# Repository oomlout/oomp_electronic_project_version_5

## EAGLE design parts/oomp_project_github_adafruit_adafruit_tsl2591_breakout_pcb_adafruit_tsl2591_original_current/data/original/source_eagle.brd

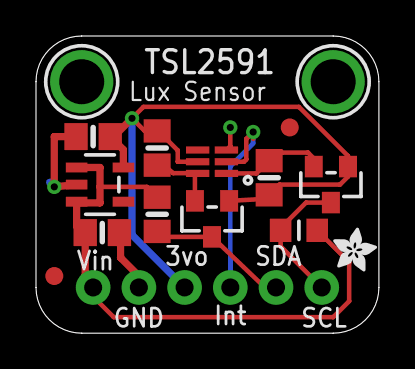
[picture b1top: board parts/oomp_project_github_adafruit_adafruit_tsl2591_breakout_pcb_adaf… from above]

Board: 2 copper layers, 19.1 x 16.5 mm, 17 parts (1 on the bottom side), 8 nets.

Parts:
C2, C3: 10uF; 0805-NO
FID1, FID2: FIDUCIAL""; FIDUCIAL_1MM
JP1: 1X06_ROUND_FULL_76
Q1, Q2: BSS138; SOT23-WIDE
R2, R3, R4: 10K; 0805-NO
R5: 10K; _0805MP
U1: TSL2591; DFN6_TAOS
U2: MIC5225-3.3; SOT23-5
U$15: ADAFRUIT_2.5MM
U$18, U$19: MOUNTINGHOLE2.5; MOUNTINGHOLE_2.5_PLATED
U$20: ADAFRUIT_5MM

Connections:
3.3V: C3.1, JP1.3, Q1.1, Q2.1, R2.2, R3.2, U1.5, U2.5
GND: C2.2, C3.2, JP1.2, U1.3, U2.2
INT: JP1.4, U1.2
SCL: JP1.6, Q2.3, R5.1
SCL_3V: Q2.2, R3.1, U1.1
SDA: JP1.5, Q1.3, R4.1
SDA_3V: Q1.2, R2.1, U1.6
VIN: C2.1, JP1.1, R4.2, R5.2, U2.1, U2.3

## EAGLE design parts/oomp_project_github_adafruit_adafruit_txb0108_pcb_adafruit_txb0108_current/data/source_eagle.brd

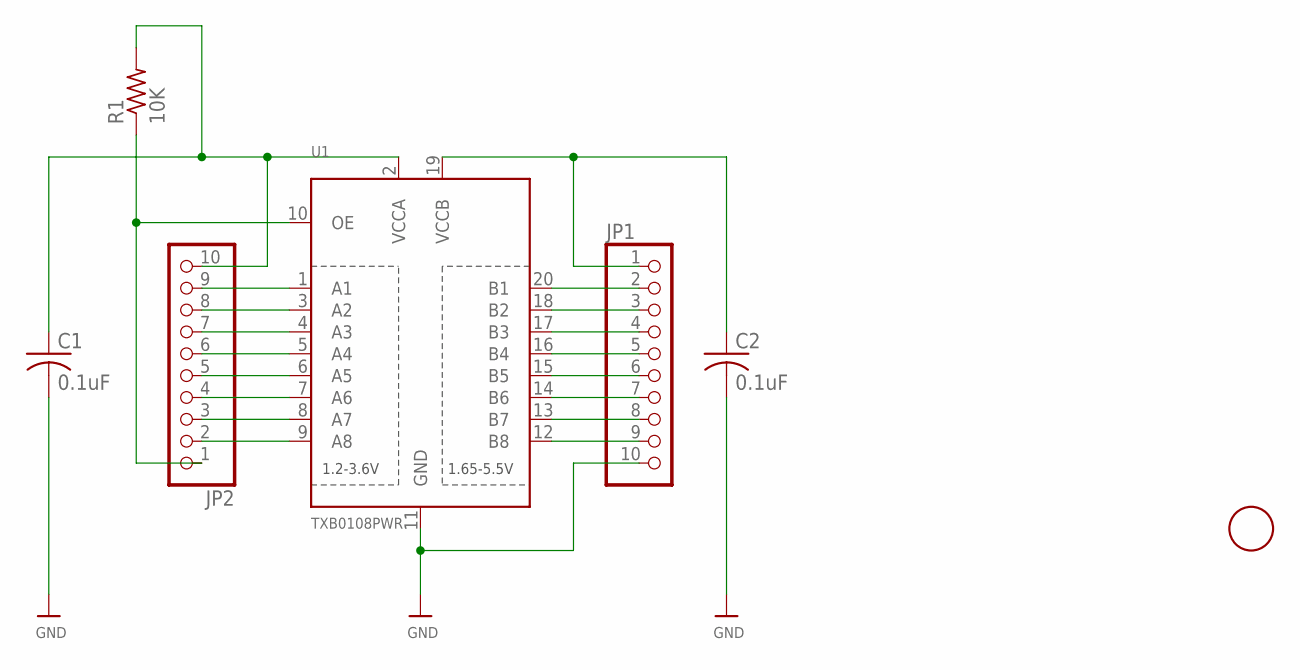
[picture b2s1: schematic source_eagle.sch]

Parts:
C1, C2: 0.1uF; C0805
JP1, JP2: HEADER-1X10THICKER; 1X10_ROUND_76
R1: 10K; R0805
U1: TXB0108PWR; TSSOP20
U$6: FIDUCIAL; FIDUCIAL_1MM

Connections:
GND: C1.2, C2.2, JP1.10, U1.11 (GND)
unnamed: JP1.9, U1.12 (B8)
unnamed: JP1.8, U1.13 (B7)
unnamed: JP1.7, U1.14 (B6)
unnamed: JP1.6, U1.15 (B5)
unnamed: JP1.5, U1.16 (B4)
unnamed: JP1.4, U1.17 (B3)
unnamed: JP1.3, U1.18 (B2)
unnamed: JP1.2, U1.20 (B1)
unnamed: C2.1, JP1.1, U1.19 (VCCB)
unnamed: C1.1, JP2.10, R1.2, U1.2 (VCCA)
unnamed: JP2.9, U1.1 (A1)
unnamed: JP2.8, U1.3 (A2)
unnamed: JP2.7, U1.4 (A3)
unnamed: JP2.6, U1.5 (A4)
unnamed: JP2.5, U1.6 (A5)
unnamed: JP2.4, U1.7 (A6)
unnamed: JP2.3, U1.8 (A7)
unnamed: JP2.2, U1.9 (A8)
unnamed: JP2.1, R1.1, U1.10 (OE)

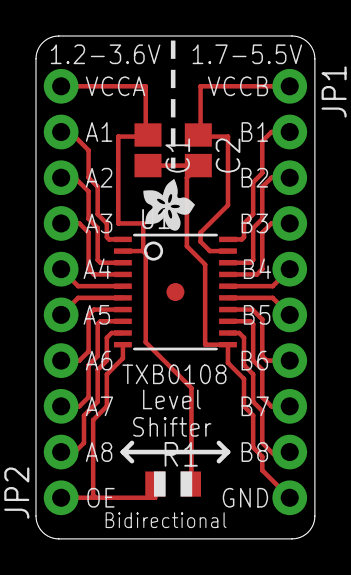
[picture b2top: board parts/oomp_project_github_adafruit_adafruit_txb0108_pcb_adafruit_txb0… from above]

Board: 2 copper layers, 15.5 x 27.9 mm, 8 parts (0 on the bottom side), 20 nets.

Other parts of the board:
U$4: ADAFRUIT200MIL

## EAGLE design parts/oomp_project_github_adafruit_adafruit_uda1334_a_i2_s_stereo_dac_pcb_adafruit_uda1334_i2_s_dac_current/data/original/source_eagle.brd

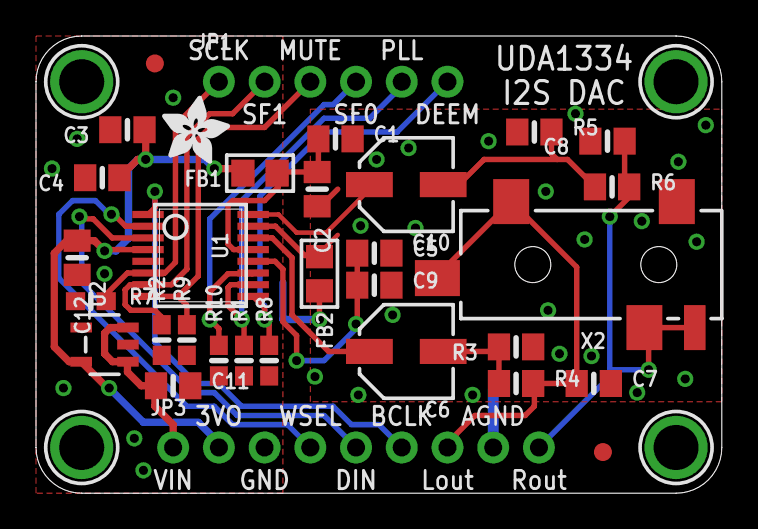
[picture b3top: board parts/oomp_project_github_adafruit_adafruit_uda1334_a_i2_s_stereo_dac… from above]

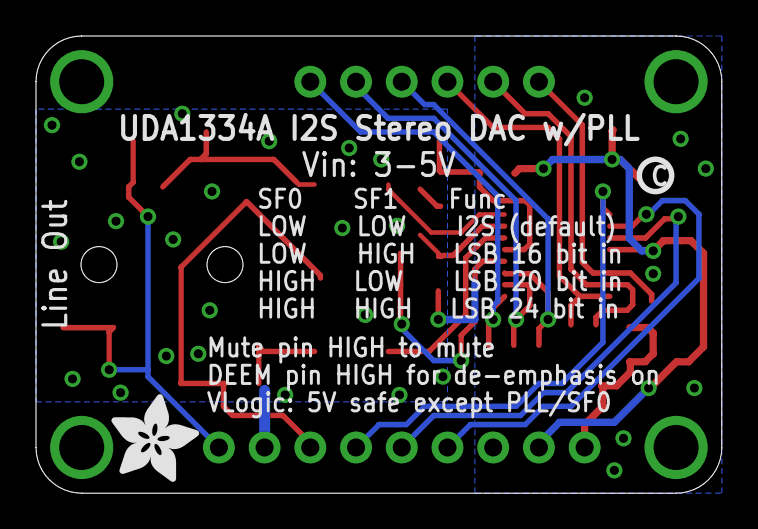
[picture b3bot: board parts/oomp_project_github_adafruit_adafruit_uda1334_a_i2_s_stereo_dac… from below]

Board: 2 copper layers, 38.1 x 25.4 mm, 38 parts (2 on the bottom side), 21 nets.

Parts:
C1, C3, C9: 0.1uF; 0805-NO
C2, C4, C5, C11, C12: 10uF; 0805-NO
C6, C10: 47uF; PANASONIC_C
C7, C8: 0.01uF; 0805-NO
FB1, FB2: Ferrite; 0805
FID1, FID2: FIDUCIAL_1MM
JP1: 1X06_ROUND_70
JP3: 1X09_ROUND_70
R1, R2, R7, R8, R9, R10: 10k; 0603-NO
R3, R5: 220k; 0805-NO
R4, R6: 100; 0805-NO
U1: UDA1334ATS; SSOP16_4.4MM
U2: MIC5225-3.3; SOT23-5
U$5: PCBFEAT-REV-040
U$6: ADAFRUIT_5MM
U$11, U$12, U$13, U$14: MOUNTINGHOLE2.5; MOUNTINGHOLE_2.5_PLATED
U$29: ADAFRUIT_3.5MM
X2: 19269; 4UCONN_19269

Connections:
3.3V: C3.1, C4.1, C12.1, FB1.2, JP3.2, U1.4, U2.5
AGND: C1.2, C2.2, C5.2, C7.2, C8.2, C9.2, FB2.1, JP3.8, R3.1, R5.1, U1.15, X2.1
BITCLK_IN: JP3.6, U1.1
DATA_IN: JP3.5, U1.3
DEEM/CLKOUT: JP1.6, R8.2, U1.9
GND: C3.2, C4.2, C11.2, C12.2, FB2.2, JP3.3, R1.1, R2.1, R7.1, R8.1, R9.1, R10.1, U1.5, U2.2
MUTE: JP1.3, R9.2, U1.8
unnamed: C5.1, C9.1, U1.12
unnamed: C1.1, C2.1, FB1.1, U1.13
unnamed: C10.+, U1.16
unnamed: C6.+, U1.14
unnamed: C6.-, R3.2, R4.1
unnamed: C10.-, R5.2, R6.1
OUTL: C7.1, JP3.7, R4.2, X2.2, X2.4
OUTR: C8.1, JP3.9, R6.2, X2.3, X2.5
PLL_IN: JP1.5, R1.2, U1.10
SFOR0: JP1.4, R10.2, U1.11
SFOR1: JP1.2, R2.2, U1.7
SYSCLK_IN: JP1.1, R7.2, U1.6
VIN: C11.1, JP3.1, U2.1, U2.3
WORDSEL_IN: JP3.4, U1.2

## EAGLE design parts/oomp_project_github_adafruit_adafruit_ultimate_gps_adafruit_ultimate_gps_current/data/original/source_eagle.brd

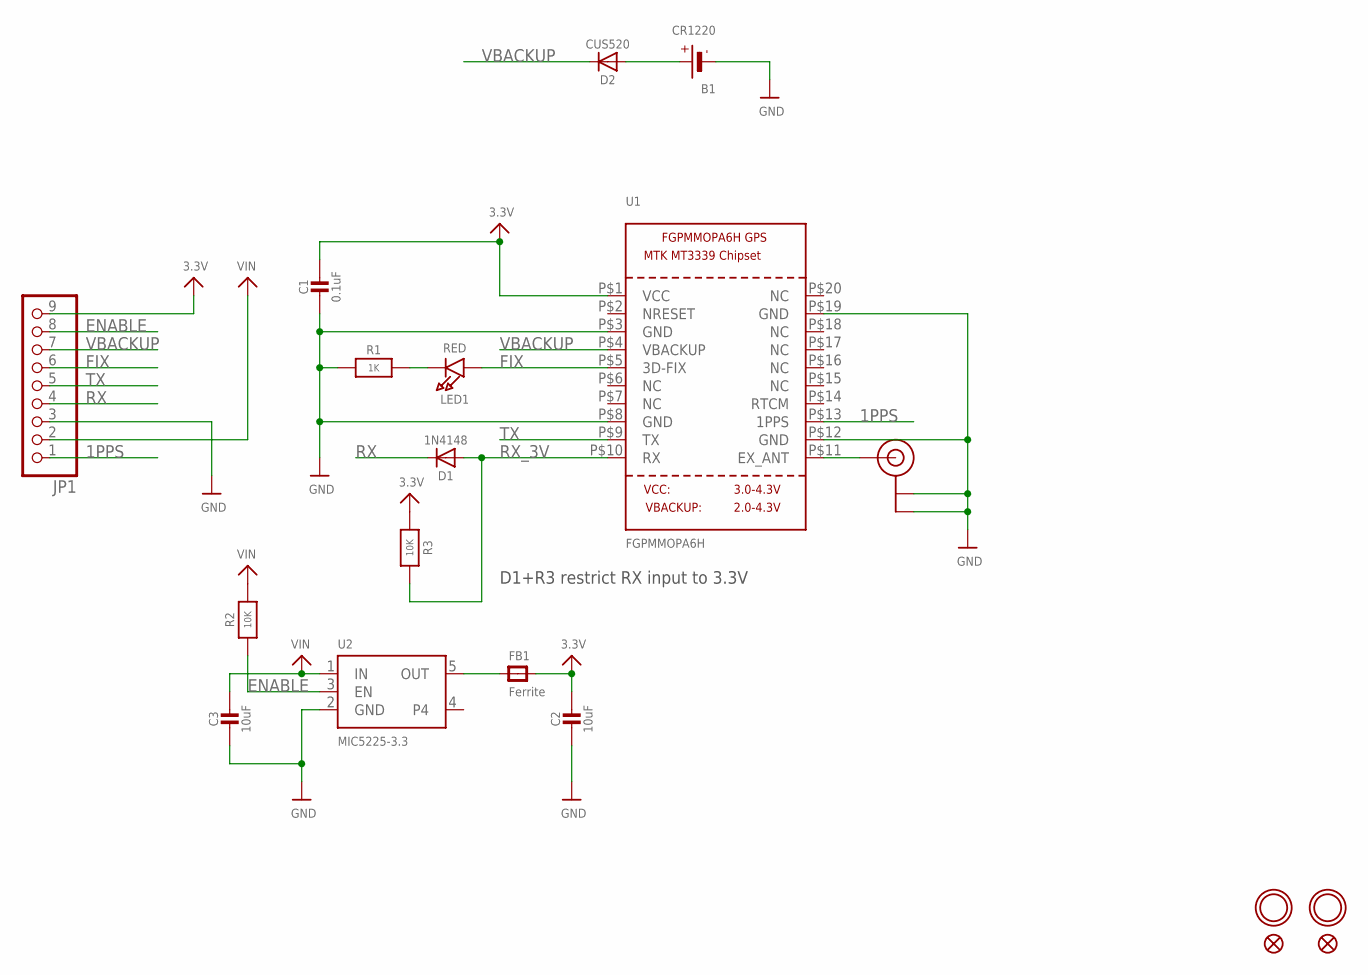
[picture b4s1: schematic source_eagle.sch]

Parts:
B1: CR1220
C1: 0.1uF; 0805-NO
C2, C3: 10uF; 0805-NO
D1: 1N4148; SOD-323
D2: CUS520; SOD-323
FB1: Ferrite; 0805-NO
FID1, FID2: FIDUCIAL""; FIDUCIAL_1MM
JP1: HEADER-1X970MIL; 1X09_ROUND_70
LED1: RED; CHIPLED_0805
R1: 1K; 0805-NO
R2, R3: 10K; 0805-NO
U1: FGPMMOPA6H
U2: MIC5225-3.3; SOT23-5
U$8, U$9: MOUNTINGHOLE2.5; MOUNTINGHOLE_2.5_PLATED
U$20: U.FL

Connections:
1PPS: JP1.1, U1.P$13 (1PPS)
3.3V: C1.1, C2.1, FB1.2, JP1.9, R3.1, U1.P$1 (VCC)
ENABLE: JP1.8, R2.1, U2.3 (EN)
FIX: JP1.6, LED1.A, U1.P$5 (3D-FIX)
GND: B1.-, C1.2, C2.2, C3.2, JP1.3, R1.1, U1.P$3 (GND), U1.P$8 (GND), U1.P$12 (GND), U1.P$19 (GND), U2.2 (GND), U$20.P$1 (GND), U$20.P$2 (GND)
unnamed: B1.+$1 (+), B1.+$2 (+), D2.A
unnamed: LED1.C, R1.2
unnamed: FB1.1, U2.5 (OUT)
unnamed: U1.P$11 (EX_ANT), U$20.P$3 (SIGNAL)
RX: D1.C, JP1.4
RX_3V: D1.A, R3.2, U1.P$10 (RX)
TX: JP1.5, U1.P$9 (TX)
VBACKUP: D2.C, JP1.7, U1.P$4 (VBACKUP)
VIN: C3.1, JP1.2, R2.2, U2.1 (IN)

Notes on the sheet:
D1+R3 restrict RX input to 3.3V

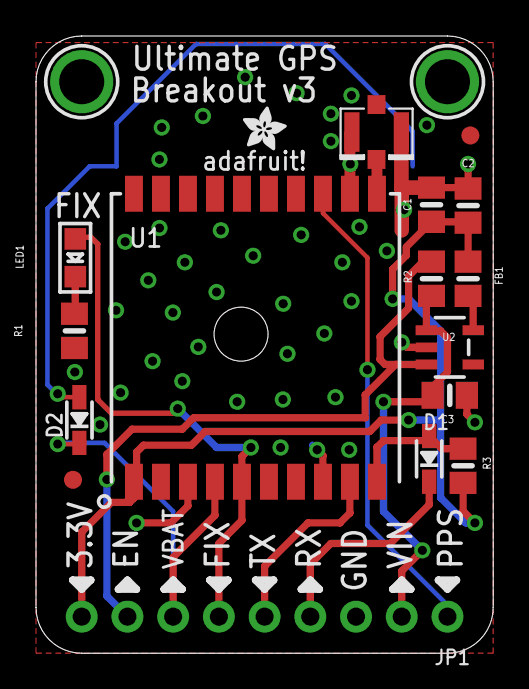
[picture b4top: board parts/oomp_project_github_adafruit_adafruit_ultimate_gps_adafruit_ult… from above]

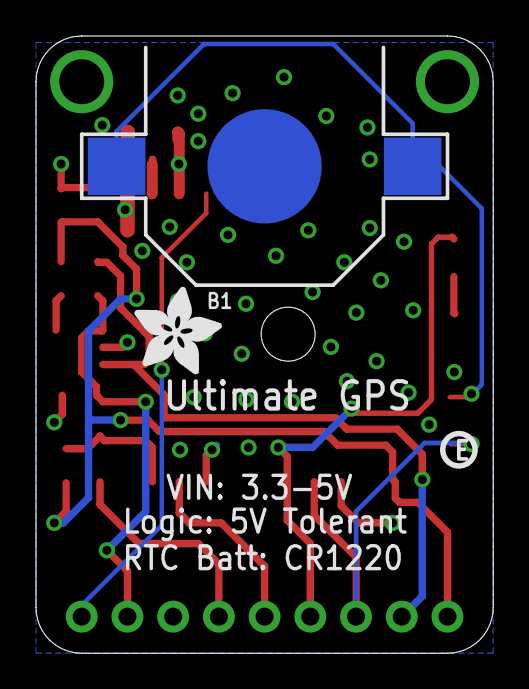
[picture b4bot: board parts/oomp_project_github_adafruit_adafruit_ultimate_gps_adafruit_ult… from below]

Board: 2 copper layers, 25.4 x 34.3 mm, 22 parts (3 on the bottom side), 14 nets.

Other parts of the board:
U$15: ADAFRUIT_2.5MM
U$16: PCBFEAT-REV-040
U$18: ADAFRUIT_5MM

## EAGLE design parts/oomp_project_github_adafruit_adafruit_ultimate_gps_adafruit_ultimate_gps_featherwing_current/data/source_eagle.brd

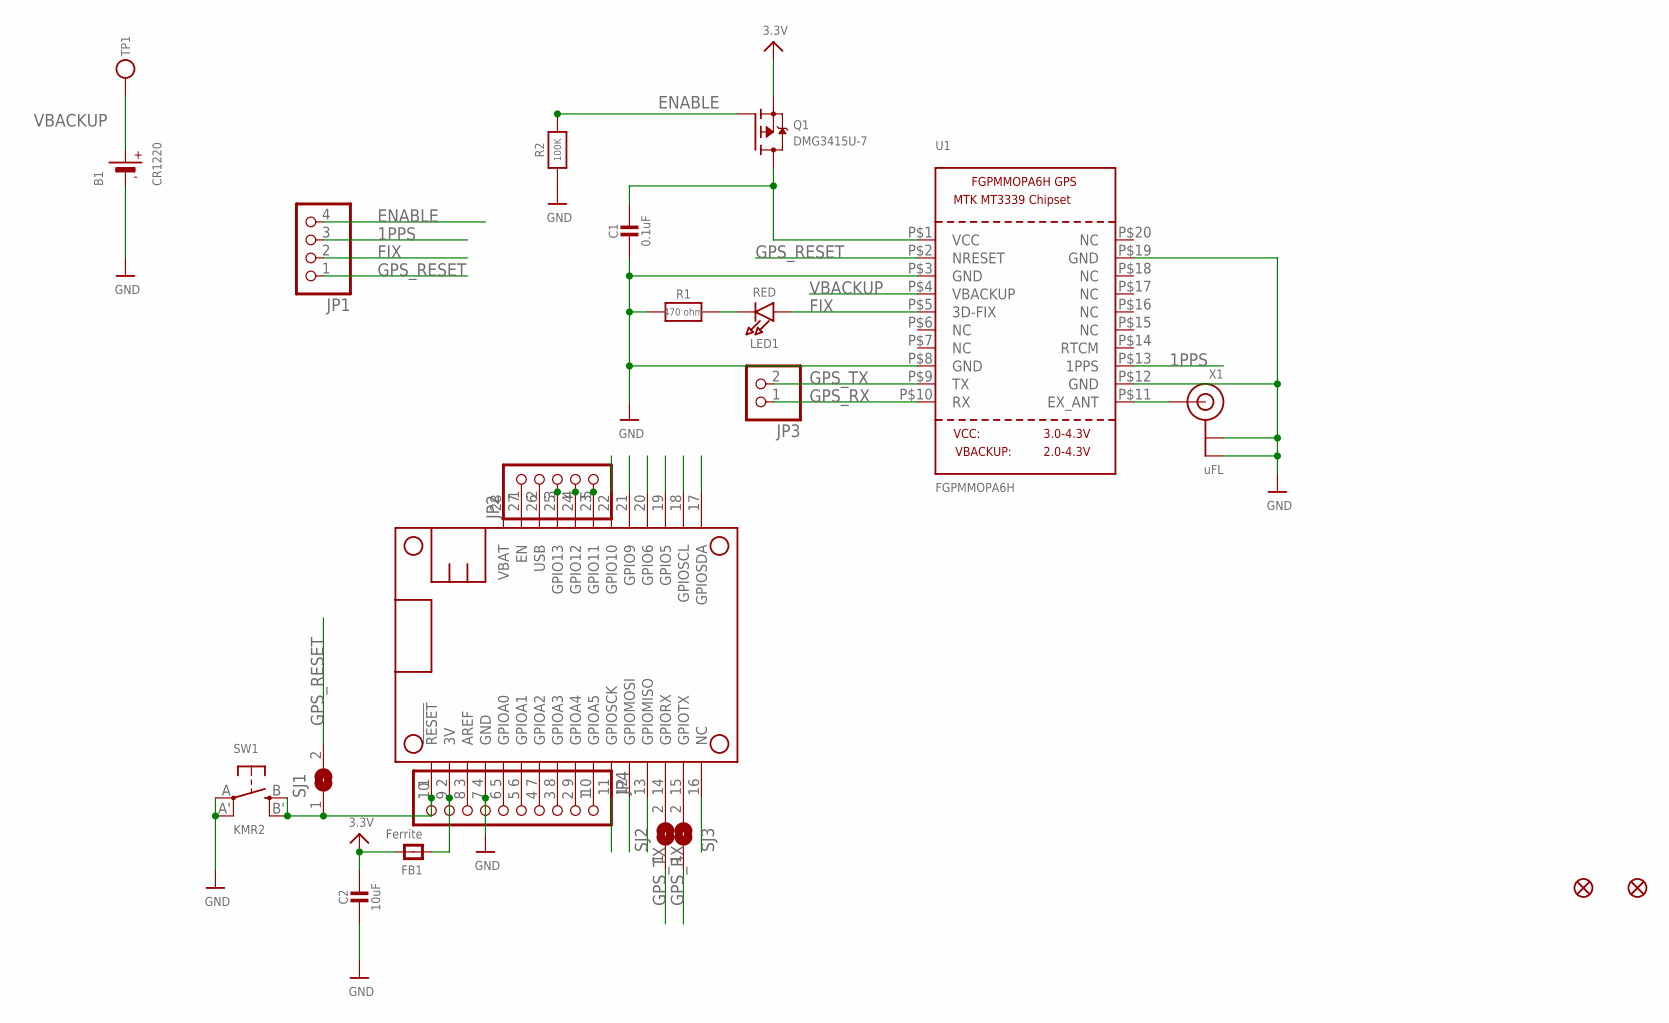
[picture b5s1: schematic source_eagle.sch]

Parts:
B1: CR1220; CR1220-2
C1: 0.1uF; 0805-NO
C2: 10uF; 0805-NO
FB1: Ferrite; 0805-NO
FID1, FID2: FIDUCIAL""; FIDUCIAL_1MM
JP1: HEADER-1X4ROUND; 1X04_ROUND
JP2: HEADER-1X570MIL; 1X05_ROUND_70
JP3: HEADER-1X2ROUND; 1X02_ROUND
JP4: HEADER-1X10ROUND; 1X10_ROUND
LED1: RED; CHIPLED_0805_NOOUTLINE
MS1: FEATHERWING
Q1: DMG3415U-7; SOT23-WIDE
R1: 470 ohm; 0805-NO
R2: 100K; 0805-NO
SJ1: SOLDERJUMPER; SOLDERJUMPER_ARROW_NOPASTE
SJ2, SJ3: SOLDERJUMPERCLOSED; SOLDERJUMPER_CLOSEDWIRE
SW1: KMR2; BTN_KMR2_4.6X2.8
TP1: TESTPOINTROUND1.5MM; TESTPOINT_ROUND_1.5MM
U1: FGPMMOPA6H
X1: uFL; U.FL

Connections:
1PPS: JP1.3, U1.P$13 (1PPS)
3.3V: C2.1, FB1.2, Q1.2 (S)
3V: FB1.1, JP4.9, MS1.2 (3V)
A: JP4.6, MS1.5 (GPIOA0)
AREF: JP4.8, MS1.3 (AREF)
B: JP4.5, MS1.6 (GPIOA1)
C: JP4.4, MS1.7 (GPIOA2)
D: JP4.3, MS1.8 (GPIOA3)
E: JP4.2, MS1.9 (GPIOA4)
EN: JP2.1, MS1.27 (EN)
ENABLE: JP1.4, Q1.1 (G), R2.2
F: JP4.1, MS1.10 (GPIOA5)
FIX: JP1.2, LED1.A, U1.P$5 (3D-FIX)
G: MS1.16 (NC)
GND: B1.-, C1.2, C2.2, JP4.7, MS1.4 (GND), R1.1, R2.1, SW1.A, SW1.A' (P1), U1.P$3 (GND), U1.P$8 (GND), U1.P$12 (GND), U1.P$19 (GND), X1.1 (GND), X1.2 (GND)
GPS_RESET: JP1.1, SJ1.2, U1.P$2 (NRESET)
GPS_RX: JP3.1, SJ3.1, U1.P$10 (RX)
GPS_TX: JP3.2, SJ2.1, U1.P$9 (TX)
H: MS1.19 (GPIO5)
I: MS1.20 (GPIO6)
J: MS1.21 (GPIO9)
K: MS1.22 (GPIO10)
L: JP2.5, MS1.23 (GPIO11)
M: JP2.4, MS1.24 (GPIO12)
MISO: MS1.13 (GPIOMISO)
MOSI: MS1.12 (GPIOMOSI)
N: JP2.3, MS1.25 (GPIO13)
unnamed: LED1.C, R1.2
unnamed: U1.P$11 (EX_ANT), X1.3 (SIGNAL)
unnamed: C1.1, Q1.3 (D), U1.P$1 (VCC)
RST: JP4.10, MS1.1 (!RESET), SJ1.1, SW1.B (S), SW1.B' (S1)
RX: MS1.14 (GPIORX), SJ2.2
SCK: MS1.11 (GPIOSCK)
SCL: MS1.18 (GPIOSCL)
SDA: MS1.17 (GPIOSDA)
TX: MS1.15 (GPIOTX), SJ3.2
USB: JP2.2, MS1.26 (USB)
VBACKUP: B1.+, TP1.P$1, U1.P$4 (VBACKUP)

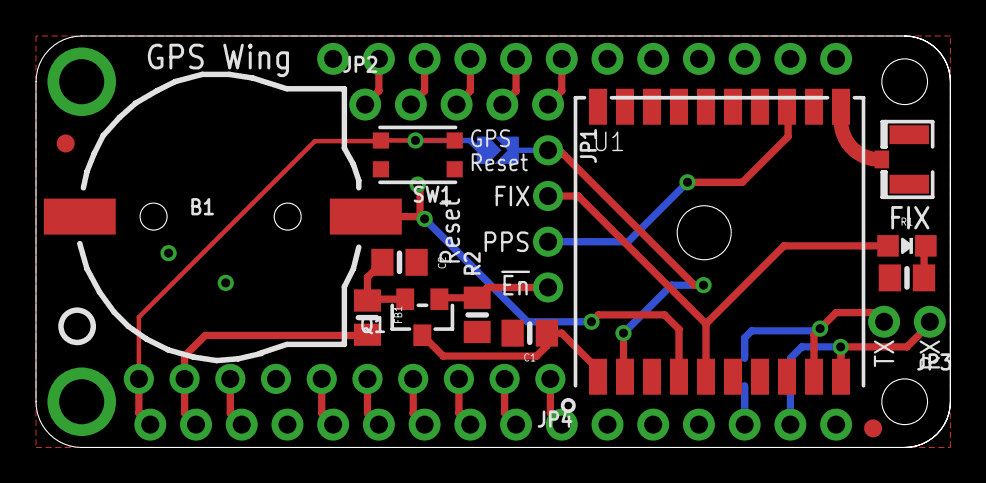
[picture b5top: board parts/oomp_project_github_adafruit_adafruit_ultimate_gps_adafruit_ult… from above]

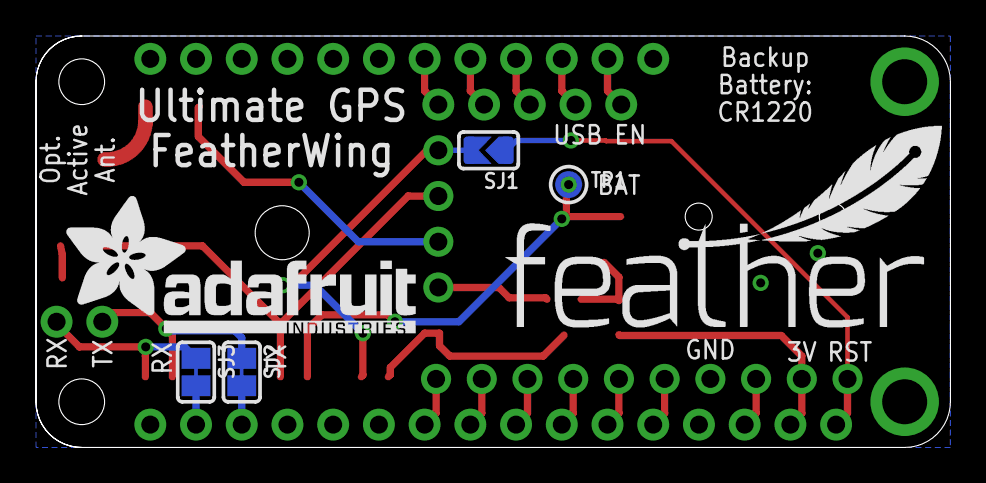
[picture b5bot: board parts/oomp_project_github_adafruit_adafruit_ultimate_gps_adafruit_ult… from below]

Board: 2 copper layers, 50.8 x 22.9 mm, 25 parts (6 on the bottom side), 28 nets.

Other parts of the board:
U$9: PCBFEAT-REV-040
U$10: FEATHERLOGO
U$11: ADAFRUIT_TEXT_20MM

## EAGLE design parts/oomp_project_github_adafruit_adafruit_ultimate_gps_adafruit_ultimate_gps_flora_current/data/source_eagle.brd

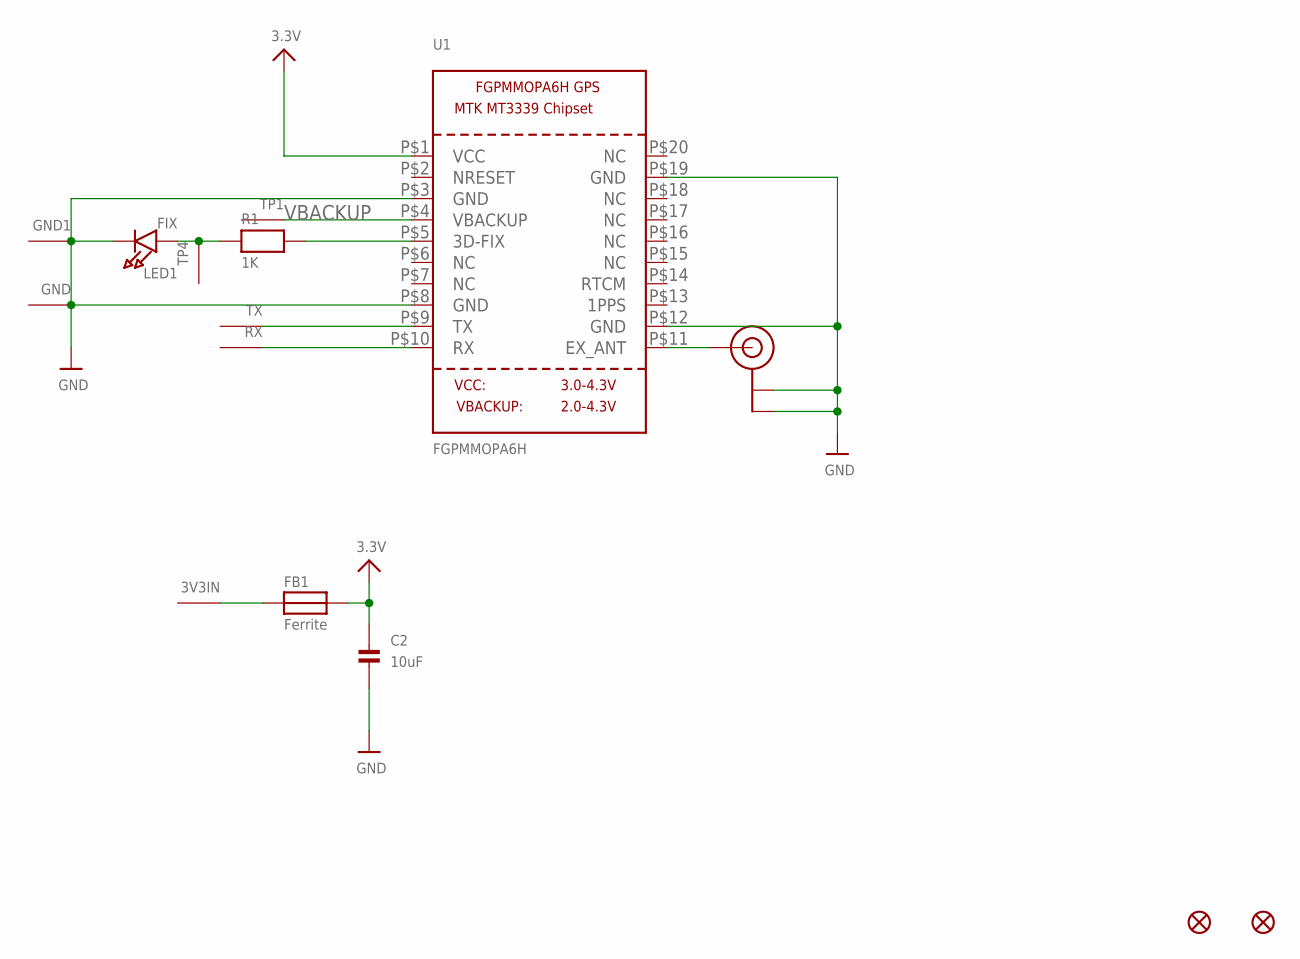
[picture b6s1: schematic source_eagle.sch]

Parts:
3V3IN: SEWTAP-2.0IN; SEWINGTAP_2.0
C2: 10uF; 0805
FB1: Ferrite; 0805
FID1, FID2: FIDUCIAL""; FIDUCIAL_1MM
GND, GND1: SEWTAP-2.0IN; SEWINGTAP_2.0
LED1: FIX; CHIPLED_0805
R1: 1K; 0805
RX: SEWTAP-2.0IN; SEWINGTAP_2.0
TP1, TP4: SEWTAP-2.0IN; SEWINGTAP_2.0
TX: SEWTAP-2.0IN; SEWINGTAP_2.0
U1: FGPMMOPA6H
U$20: U.FL

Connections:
3.3V: C2.1, FB1.2, U1.P$1 (VCC)
GND: C2.2, GND.P$1, GND1.P$1, LED1.C, U1.P$3 (GND), U1.P$8 (GND), U1.P$12 (GND), U1.P$19 (GND), U$20.P$1 (GND), U$20.P$2 (GND)
unnamed: LED1.A, R1.1, TP4.P$1
unnamed: R1.2, U1.P$5 (3D-FIX)
unnamed: 3V3IN.P$1, FB1.1
unnamed: U1.P$11 (EX_ANT), U$20.P$3 (SIGNAL)
RX: RX.P$1, U1.P$10 (RX)
TX: TX.P$1, U1.P$9 (TX)
VBACKUP: TP1.P$1, U1.P$4 (VBACKUP)

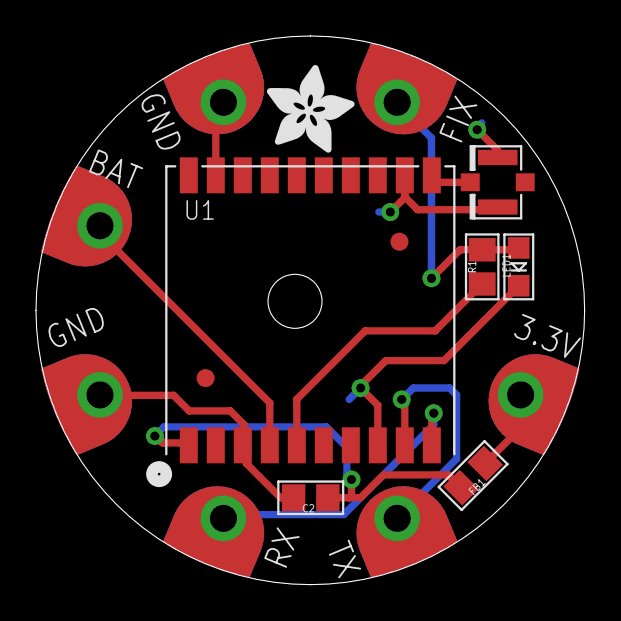
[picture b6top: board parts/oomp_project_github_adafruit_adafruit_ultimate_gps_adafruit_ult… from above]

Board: 2 copper layers, 30.5 x 30.5 mm, 17 parts (1 on the bottom side), 9 nets.

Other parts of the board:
U$6: ADAFRUIT_5MM
U$7: FLORASMALL

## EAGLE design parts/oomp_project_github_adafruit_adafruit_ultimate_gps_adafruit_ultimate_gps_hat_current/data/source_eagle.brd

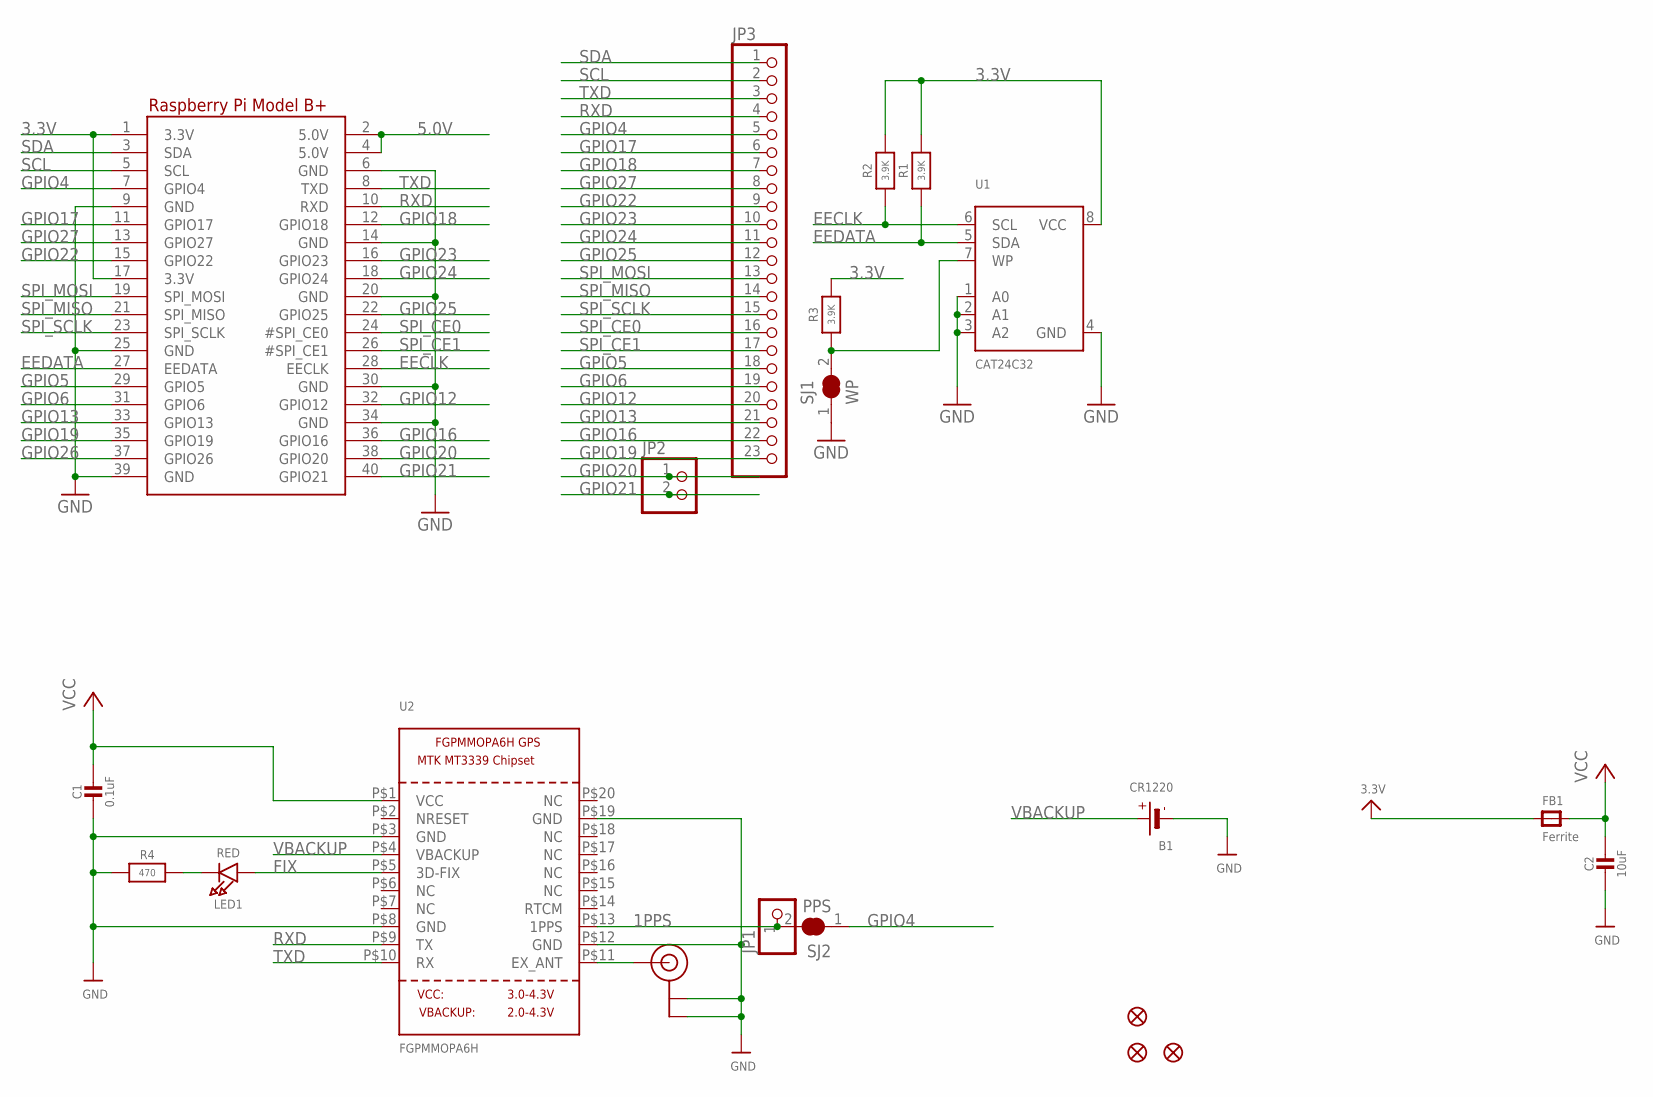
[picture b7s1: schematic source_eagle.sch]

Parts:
B1: CR1220
C1: 0.1uF; 0805-NO
C2: 10uF; 0805-NO
FB1: Ferrite; 0805
FID1, FID2, FID3: FIDUCIAL_1MM
JP1: PINHD-1X1CB; 1X01-CLEANBIG
JP2: HEADER-1X2ROUND; 1X02_ROUND
JP3: HEADER-1X23; 1X23_ROUND_70MIL
LED1: RED; CHIPLED_0805
R1, R2, R3: 3.9K; 0805-NO
R4: 470; 0805-NO
RPI1: RASPBERRYPI_BPLUS_HATSLOTS; PI_HAT_SLOTS
SJ1: WP; SOLDERJUMPER_CLOSEDWIRE
SJ2: PPS; SOLDERJUMPER_CLOSEDWIRE
U1: CAT24C32; SOIC8_150MIL
U2: FGPMMOPA6H
U$20: U.FL

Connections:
1PPS: JP1.1, SJ2.2, U2.P$13 (1PPS)
3.3V: FB1.1, R1.2, R2.2, R3.2, RPI1.1 (3.3V), RPI1.17 (3.3V), U1.8 (VCC)
5.0V: RPI1.2 (5.0V), RPI1.4 (5.0V)
EECLK: R2.1, RPI1.28 (EECLK), U1.6 (SCL)
EEDATA: R1.1, RPI1.27 (EEDATA), U1.5 (SDA)
FIX: LED1.A, U2.P$5 (3D-FIX)
GND: B1.-, C1.2, C2.2, R4.1, RPI1.6 (GND), RPI1.9 (GND), RPI1.14 (GND), RPI1.20 (GND), RPI1.25 (GND), RPI1.30 (GND), RPI1.34 (GND), RPI1.39 (GND), SJ1.1, U1.1 (A0), U1.2 (A1), U1.3 (A2), U1.4 (GND), U2.P$3 (GND), U2.P$8 (GND), U2.P$12 (GND), U2.P$19 (GND), U$20.P$1 (GND), U$20.P$2 (GND)
GPIO4: JP3.5, RPI1.7 (GPIO4), SJ2.1
GPIO5: JP3.18, RPI1.29 (GPIO5)
GPIO6: JP3.19, RPI1.31 (GPIO6)
GPIO12: JP3.20, RPI1.32 (GPIO12)
GPIO13: JP3.21, RPI1.33 (GPIO13)
GPIO16: JP3.22, RPI1.36 (GPIO16)
GPIO17: JP3.6, RPI1.11 (GPIO17)
GPIO18: JP3.7, RPI1.12 (GPIO18)
GPIO19: JP3.23, RPI1.35 (GPIO19)
GPIO20: JP2.1, RPI1.38 (GPIO20)
GPIO21: JP2.2, RPI1.40 (GPIO21)
GPIO22: JP3.9, RPI1.15 (GPIO22)
GPIO23: JP3.10, RPI1.16 (GPIO23)
GPIO24: JP3.11, RPI1.18 (GPIO24)
GPIO25: JP3.12, RPI1.22 (GPIO25)
GPIO26: RPI1.37 (GPIO26)
GPIO27: JP3.8, RPI1.13 (GPIO27)
unnamed: R3.1, SJ1.2, U1.7 (WP)
unnamed: LED1.C, R4.2
unnamed: U2.P$11 (EX_ANT), U$20.P$3 (SIGNAL)
RXD: JP3.4, RPI1.10 (RXD), U2.P$9 (TX)
SCL: JP3.2, RPI1.5 (SCL)
SDA: JP3.1, RPI1.3 (SDA)
SPI_CE0: JP3.16, RPI1.24 (#SPI_CE0)
SPI_CE1: JP3.17, RPI1.26 (#SPI_CE1)
SPI_MISO: JP3.14, RPI1.21 (SPI_MISO)
SPI_MOSI: JP3.13, RPI1.19 (SPI_MOSI)
SPI_SCLK: JP3.15, RPI1.23 (SPI_SCLK)
TXD: JP3.3, RPI1.8 (TXD), U2.P$10 (RX)
VBACKUP: B1.+$1 (+), B1.+$2 (+), U2.P$4 (VBACKUP)
VCC: C1.1, C2.1, FB1.2, U2.P$1 (VCC)

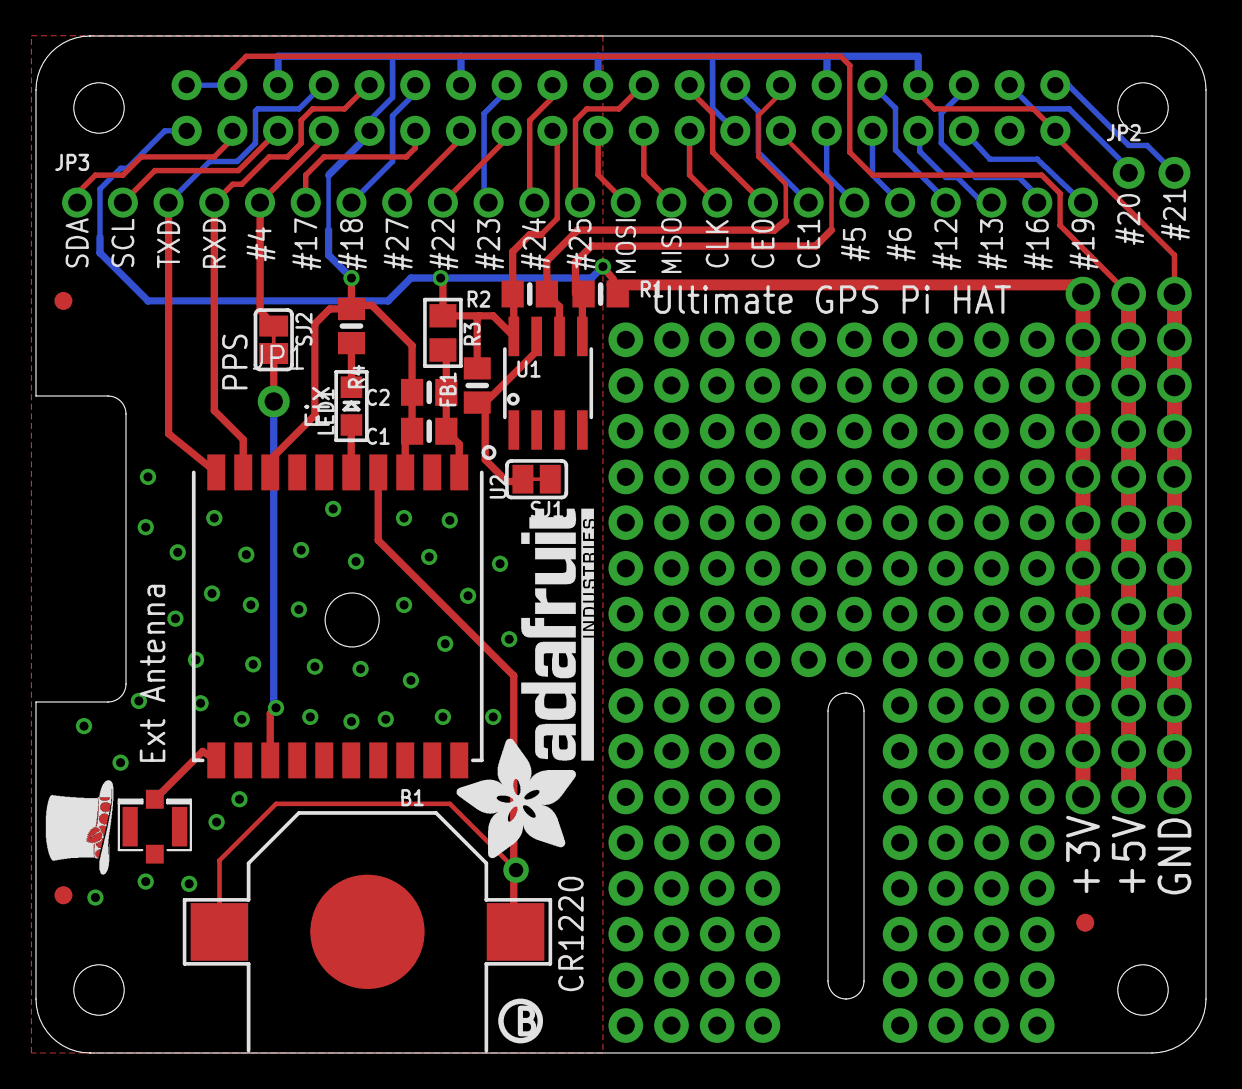
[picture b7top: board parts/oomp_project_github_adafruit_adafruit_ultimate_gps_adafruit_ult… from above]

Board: 2 copper layers, 65.0 x 56.5 mm, 24 parts (0 on the bottom side), 37 nets.

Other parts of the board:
U$3: ADAFRUIT_TEXT_20MM
U$4: PIHATLOGO
U$6: PCBFEAT-REV-056

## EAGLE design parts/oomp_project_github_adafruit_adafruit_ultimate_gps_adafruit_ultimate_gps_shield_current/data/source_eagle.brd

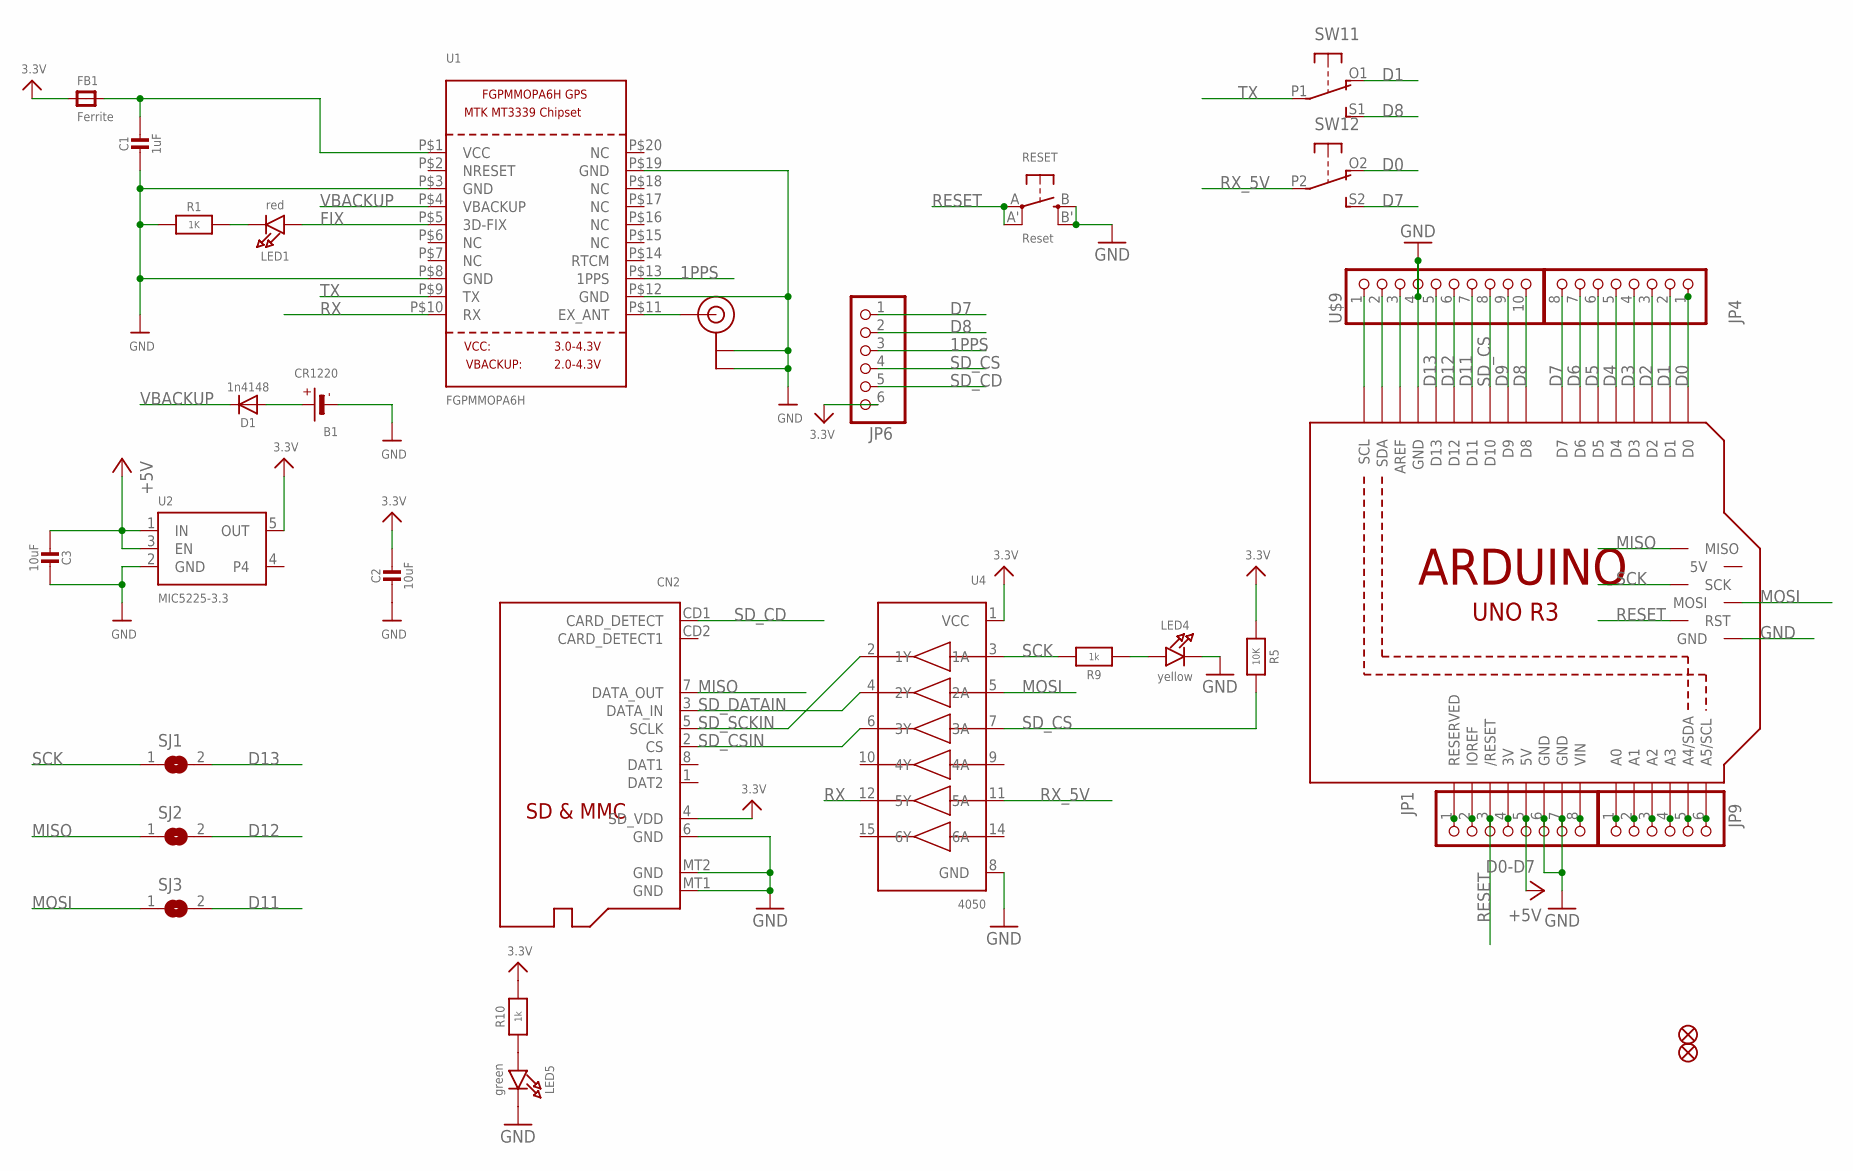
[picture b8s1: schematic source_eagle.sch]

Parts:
B1: CR1220
C1: 1uF; 0805-NO
C2, C3: 10uF; 0805-NO
CN2: MICROSD
D1: 1n4148; SOD-323
FB1: Ferrite; 0805
FID1, FID2: FIDUCIAL""; FIDUCIAL_1MM
JP1: D0-D7; 1X08-BIG
JP4: PINHD-1X8BIG; 1X08-BIG
JP6, JP9: PINHD-1X6B; 1X06-BIG
LED1: red; CHIPLED_0805_NOOUTLINE
LED4: yellow; CHIPLED_0805_NOOUTLINE
LED5: green; CHIPLED_0805_NOOUTLINE
M1: ARDUINO_R3_ICSP_NODIM; ARDUINOR3_ICSP_NODIM
R1: 1K; 0805-NO
R5: 10K; 0805-NO
R9, R10: 1k; 0805-NO
RESET: Reset; EVQ-Q2
SJ1, SJ2, SJ3: SOLDERJUMPER; SOLDERJUMPER_ARROW_NOPASTE
SW1: DPDT-EG1390; EG1390
U1: FGPMMOPA6H
U2: MIC5225-3.3; SOT23-5
U4: 4050; SOIC16
U$9: PINHD-1X10; 1X10-BIG
U$20: U.FL

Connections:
1PPS: JP6.3, U1.P$13 (1PPS)
3.3V: C2.1, CN2.4 (SD_VDD), FB1.1, JP6.6, R5.1, R10.2, U2.5 (OUT), U4.1 (VCC)
3V: JP1.4, M1.3V
+5V: C3.1, JP1.5, M1.5V, U2.1 (IN), U2.3 (EN)
A0: JP9.1, M1.A0
A1: JP9.2, M1.A1
A2: JP9.3, M1.A2
A3: JP9.4, M1.A3
A4: JP9.5, M1.A4 (A4/SDA)
A5: JP9.6, M1.A5 (A5/SCL)
AREF: M1.AREF, U$9.3
D0: JP4.1, M1.D0, SW1.O2 (O)
D1: JP4.2, M1.D1, SW1.O1 (O)
D2: JP4.3, M1.D2
D3: JP4.4, M1.D3
D4: JP4.5, M1.D4
D5: JP4.6, M1.D5
D6: JP4.7, M1.D6
D7: JP4.8, JP6.1, M1.D7, SW1.S2 (S)
D8: JP6.2, M1.D8, SW1.S1 (S), U$9.10
D9: M1.D9, U$9.9
D11: M1.D11, SJ3.2, U$9.7
D12: M1.D12, SJ2.2, U$9.6
D13: M1.D13, SJ1.2, U$9.5
FIX: LED1.A, U1.P$5 (3D-FIX)
GND: B1.-, C1.2, C2.2, C3.2, CN2.6 (GND), CN2.MT1 (GND), CN2.MT2 (GND), JP1.6, JP1.7, LED4.C, LED5.C, M1.GND, M1.GND@1 (GND), M1.GND@2 (GND), M1.GND@3 (GND), R1.1, RESET.B (S), RESET.B' (S1), U1.P$3 (GND), U1.P$8 (GND), U1.P$12 (GND), U1.P$19 (GND), U2.2 (GND), U4.8 (GND), U$9.4, U$20.P$1 (GND), U$20.P$2 (GND)
IOREF: JP1.2, M1.IOREF
MISO: CN2.7 (DATA_OUT), M1.MISO, SJ2.1
MOSI: M1.MOSI, SJ3.1, U4.5 (2A)
unnamed: C1.1, FB1.2, U1.P$1 (VCC)
unnamed: LED1.C, R1.2
unnamed: B1.+$1 (+), B1.+$2 (+), D1.A
unnamed: U1.P$11 (EX_ANT), U$20.P$3 (SIGNAL)
unnamed: LED4.A, R9.1
unnamed: LED5.A, R10.1
NC: JP1.1, M1.RESERVED
RESET: JP1.3, M1.RESET (/RESET), M1.RESET_ICSP (RST), RESET.A, RESET.A' (P1)
RX: U1.P$10 (RX), U4.12 (5Y)
RX_5V: SW1.P2, U4.11 (5A)
SCK: M1.SCK, R9.2, SJ1.1, U4.3 (1A)
SCL: M1.SCL, U$9.1
SDA: M1.SDA, U$9.2
SD_CD: CN2.CD1 (CARD_DETECT), JP6.5
SD_CS: JP6.4, M1.D10, R5.2, U4.7 (3A), U$9.8
SD_CSIN: CN2.2 (CS), U4.6 (3Y)
SD_DATAIN: CN2.3 (DATA_IN), U4.4 (2Y)
SD_SCKIN: CN2.5 (SCLK), U4.2 (1Y)
TX: SW1.P1, U1.P$9 (TX)
VBACKUP: D1.C, U1.P$4 (VBACKUP)
VIN: JP1.8, M1.VIN

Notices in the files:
parts and their libraries:
microbuilder: This work is placed in the public domain, and may be freely used for commercial and non-commercial work with the following conditions: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
